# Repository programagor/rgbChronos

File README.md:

# rgbChronos
New version of uChronos, using fewer LEDs, but more rainbow

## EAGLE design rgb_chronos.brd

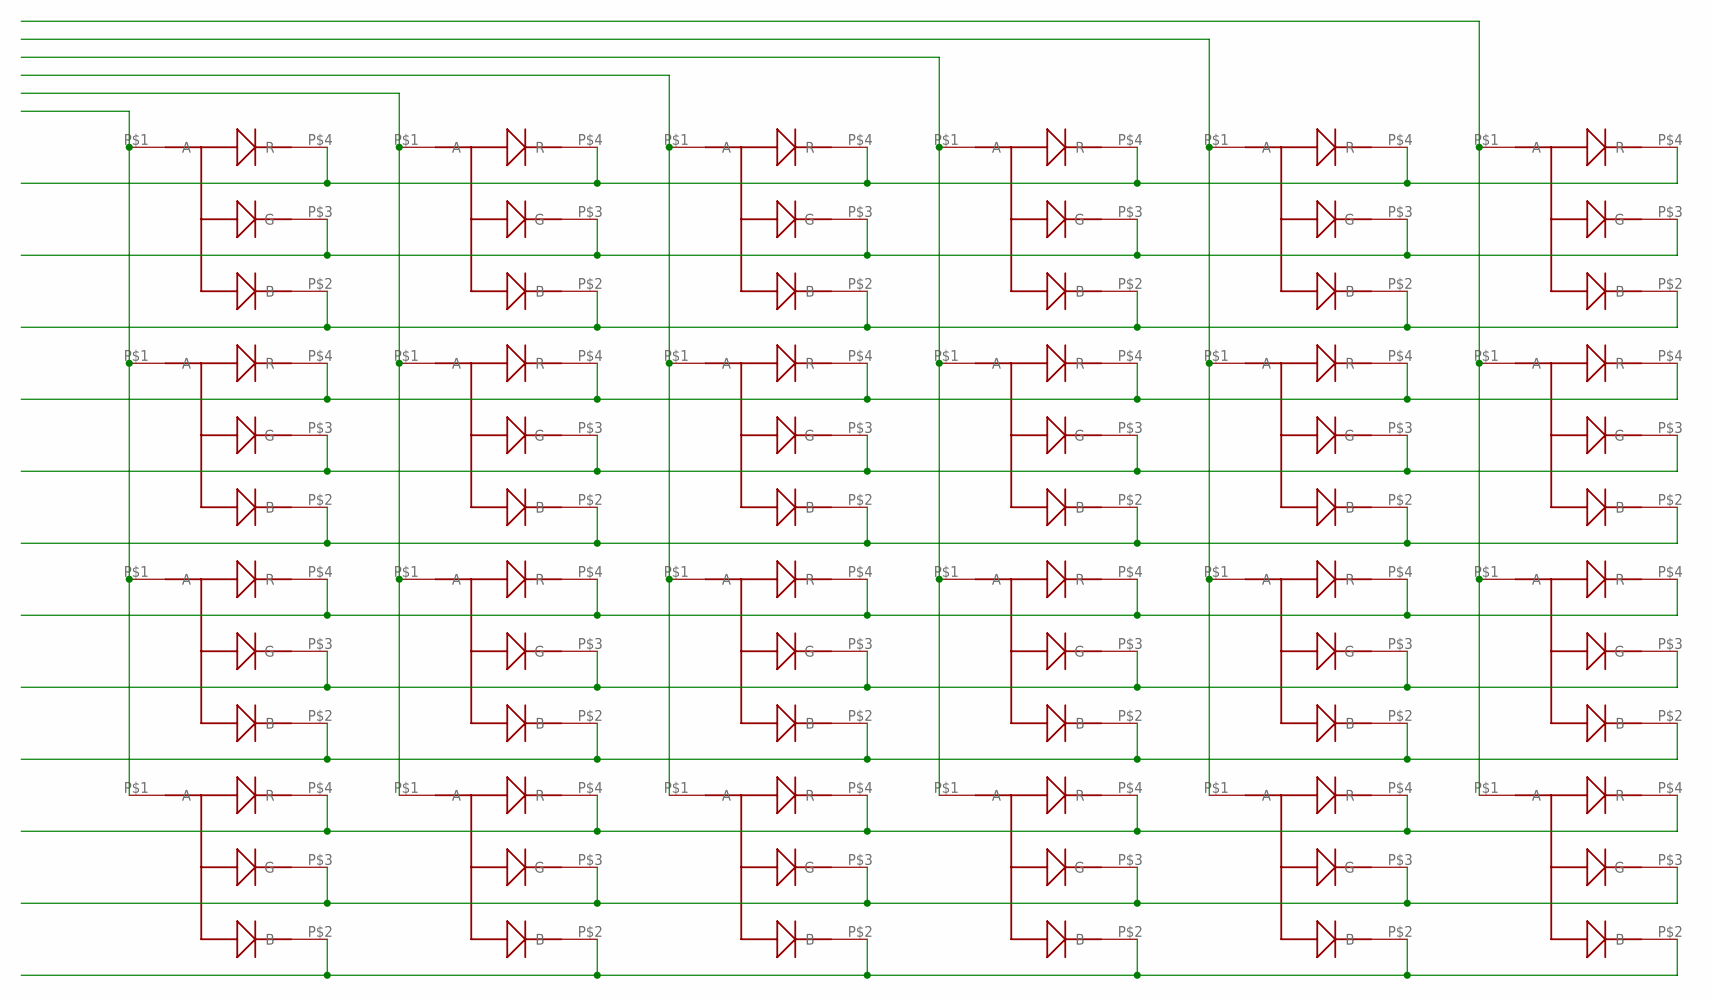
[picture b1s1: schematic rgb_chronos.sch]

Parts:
U$1, U$2, U$3, U$4, U$5, U$6, U$7, U$8, U$9, U$10, U$11, U$12, U$13, U$14, U$15, U$16, U$17, U$18, U$19, U$20, U$21, U$22, U$23, U$24: ASMB-MTB0-0A3A2; PLCC4-LED

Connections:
COL0: U$1.P$1 (A), U$2.P$1 (A), U$3.P$1 (A), U$4.P$1 (A)
COL1: U$5.P$1 (A), U$6.P$1 (A), U$7.P$1 (A), U$8.P$1 (A)
COL2: U$9.P$1 (A), U$10.P$1 (A), U$11.P$1 (A), U$12.P$1 (A)
COL3: U$13.P$1 (A), U$14.P$1 (A), U$15.P$1 (A), U$16.P$1 (A)
COL4: U$17.P$1 (A), U$18.P$1 (A), U$19.P$1 (A), U$20.P$1 (A)
COL5: U$21.P$1 (A), U$22.P$1 (A), U$23.P$1 (A), U$24.P$1 (A)
ROW0_B: U$1.P$2 (B), U$5.P$2 (B), U$9.P$2 (B), U$13.P$2 (B), U$17.P$2 (B), U$21.P$2 (B)
ROW0_G: U$1.P$3 (G), U$5.P$3 (G), U$9.P$3 (G), U$13.P$3 (G), U$17.P$3 (G), U$21.P$3 (G)
ROW0_R: U$1.P$4 (R), U$5.P$4 (R), U$9.P$4 (R), U$13.P$4 (R), U$17.P$4 (R), U$21.P$4 (R)
ROW1_B: U$2.P$2 (B), U$6.P$2 (B), U$10.P$2 (B), U$14.P$2 (B), U$18.P$2 (B), U$22.P$2 (B)
ROW1_G: U$2.P$3 (G), U$6.P$3 (G), U$10.P$3 (G), U$14.P$3 (G), U$18.P$3 (G), U$22.P$3 (G)
ROW1_R: U$2.P$4 (R), U$6.P$4 (R), U$10.P$4 (R), U$14.P$4 (R), U$18.P$4 (R), U$22.P$4 (R)
ROW2_B: U$3.P$2 (B), U$7.P$2 (B), U$11.P$2 (B), U$15.P$2 (B), U$19.P$2 (B), U$23.P$2 (B)
ROW2_G: U$3.P$3 (G), U$7.P$3 (G), U$11.P$3 (G), U$15.P$3 (G), U$19.P$3 (G), U$23.P$3 (G)
ROW2_R: U$3.P$4 (R), U$7.P$4 (R), U$11.P$4 (R), U$15.P$4 (R), U$19.P$4 (R), U$23.P$4 (R)
ROW3_B: U$4.P$2 (B), U$8.P$2 (B), U$12.P$2 (B), U$16.P$2 (B), U$20.P$2 (B), U$24.P$2 (B)
ROW3_G: U$4.P$3 (G), U$8.P$3 (G), U$12.P$3 (G), U$16.P$3 (G), U$20.P$3 (G), U$24.P$3 (G)
ROW3_R: U$4.P$4 (R), U$8.P$4 (R), U$12.P$4 (R), U$16.P$4 (R), U$20.P$4 (R), U$24.P$4 (R)

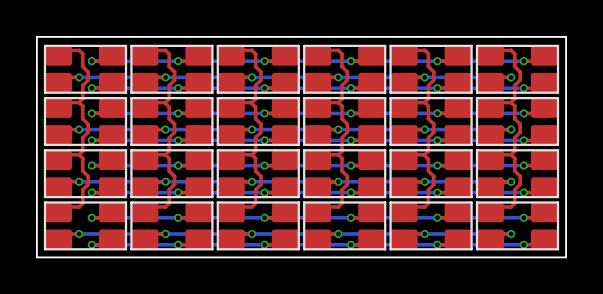
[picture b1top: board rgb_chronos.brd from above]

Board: 4 copper layers, 29.4 x 12.2 mm, 24 parts (0 on the bottom side), 18 nets.

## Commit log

2017-11-14 Empty schematics and board created
2017-11-14 LEDs added to dircuit and board
    Multiplexing implemented
2017-11-14 Display self-routed
2017-11-14 Wire width increased
2017-11-14 Display nets renamed
2017-11-15 Added LED part number
